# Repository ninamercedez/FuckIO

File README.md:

# FuckIO
An opensource fucking machine, that is far superiour to anything on the market.

## Specs
* Easy to built just with a 3D-printer, screwdrivers and easy-to-source parts.
* Completely 3D-printable with easy to print parts and almost no supports. Also avoiding tight tolerances to make this accessable as possible. 
* Simple, yet verastile mechanics.
* Based on a linear position drive, not a crank mechanism.
* Double 24V PWM output to drive external systems. Could be lube pumps, vibrators, etc.

## Mechanics
The mechanics is a direct derivative of an other open source project called OSSM. You can also find some informations about this build on their Discord.
https://github.com/KinkyMakers/OSSM-hardware

The motor mount is designed for a NEMA23 servo or stepper motor. Any motor fitting to this standart should work. 

### BOM
* iHSV57-30-18-36-... integrated servo motor from JMC
* 24V Power Brick Mean Well GST280A24-C6P 
* 40cm MGN12H linear rail
* 4x 605-2RS Z2 bearings
* Micro Switch
* GT2 20 Tooth Pulley for 8mm Axis and a 10mm belt
* GT2 belt with 10mm width
* Various M3 and M5 screws and nuts
* Arduino Nano33 IoT

## Electronics
The electronics board is used to interface an external stepper or servo controller. I can't drive a motor directly. It is based around an Arduino Nano33 IoT to enable BLE or WiFi support. It sends 5V DIR, PUL, ENA signals and expects FAULT signal and a homing switch. Two MOSFETs with freewheeling diodes allow PWM control of external systems running of the 24V supply.

## Firmware
The firmware uses a self developed stepper library. It uses the SAMD21 timer perihperials to generate the PUL signal. That way it is possible to create a much higher step rate with no processor loading. Popular Arduino libraries like AccelStepper are not up to the task.

__Do not use this firmware! It is heavly beeing worked on. It will destroy your hardware!__

## Control Software
No control software yet. But it is planned to use node-red in combination with MQTT messages.

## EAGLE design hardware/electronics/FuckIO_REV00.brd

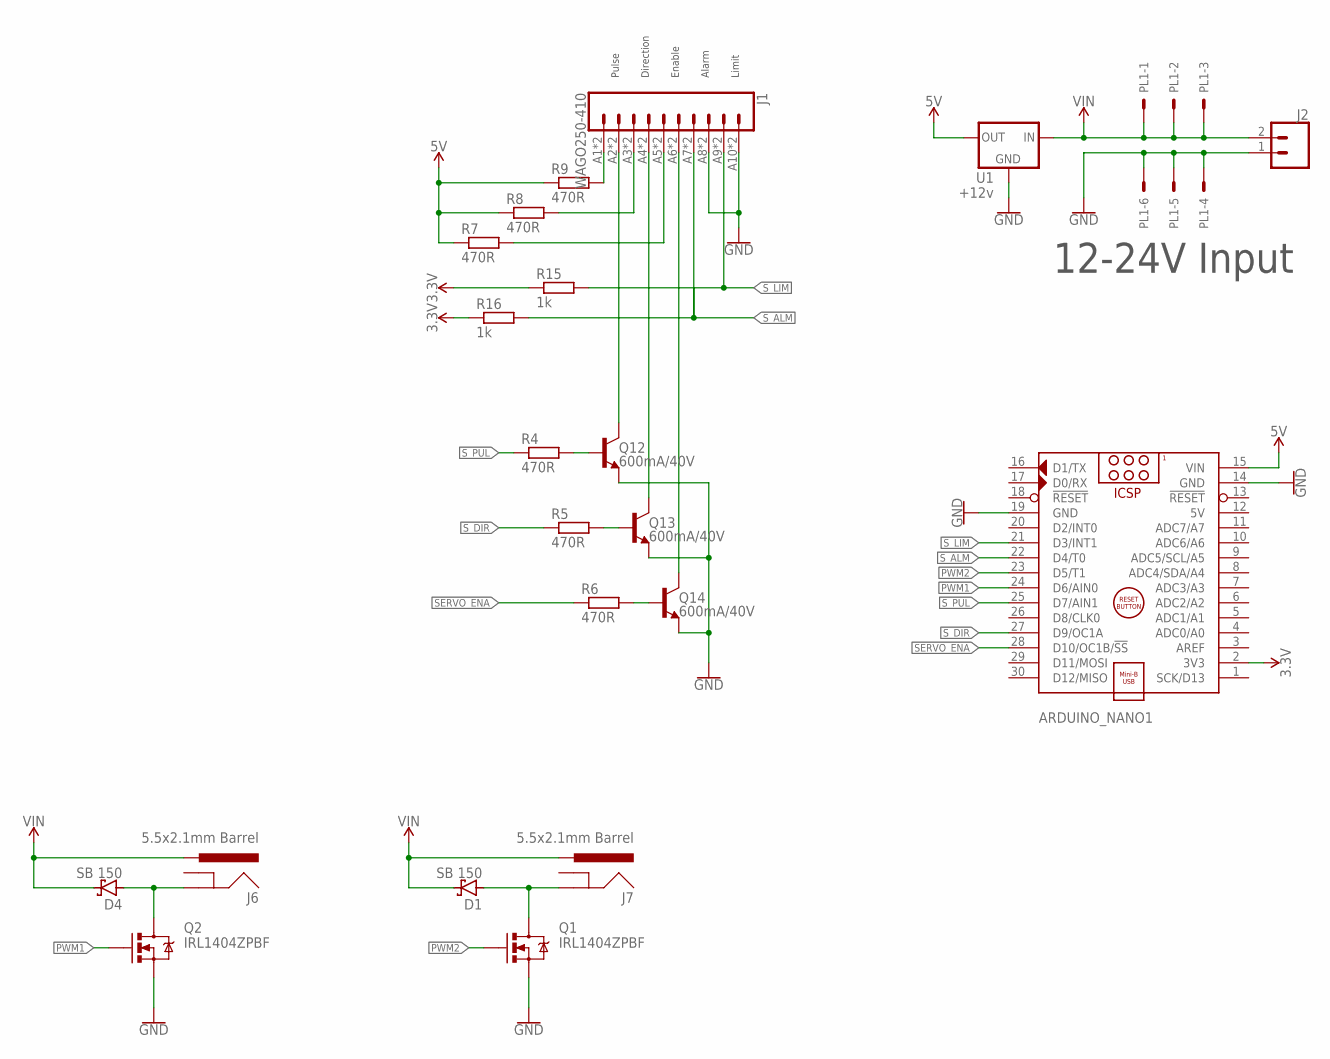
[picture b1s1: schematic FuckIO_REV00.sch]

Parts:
ARDUINO_NANO1: ARDUINO_NANO; ARDUINONANOV30_ARDUINO_NANO
D1, D4: SB 150; DIODE_DO41-10
J1: WAGO250-410; BEE_WAGO250-410
J2: CONN_025MM; SPARKFUN-CONNECTORS_SCREWTERMINAL-5MM-2
J6, J7: 5.5x2.1mm Barrel; SPARKFUN-CONNECTORS_POWER_JACK_PTH
PL1: CON-MOLEX-2_555X-6H; CON-MOLEX-2_5569-6
Q1, Q2: IRL1404ZPBF; BEE_TO220-IGO
Q12, Q13, Q14: 600mA/40V; SPARKFUN-DISCRETESEMI_TO-92
R4, R5, R6, R7, R8, R9: 470R; RCL_0204/5
R15, R16: 1k; RCL_0204/5
U1: +12v; SPARKFUN-IC-POWER_TO220-IGO

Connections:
3.3V: ARDUINO_NANO1.2 (3V3), R15.1, R16.1
5V: ARDUINO_NANO1.12 (5V), ARDUINO_NANO1.15 (VIN), R7.1, R8.1, R9.1, U1.OUT
GND: ARDUINO_NANO1.14 (GND), ARDUINO_NANO1.19 (GND), J1.A8 (8), J1.A10 (10), J1.B8 (8), J1.B10 (10), J2.1, PL1.4, PL1.5, PL1.6, Q1.S, Q2.S, Q12.3 (E), Q13.3 (E), Q14.3 (E), U1.GND
unnamed: J1.A5 (5), J1.B5 (5), R7.2
unnamed: J1.A3 (3), J1.B3 (3), R8.2
unnamed: J1.A1 (1), J1.B1 (1), R9.2
unnamed: J1.A6 (6), J1.B6 (6), Q14.1 (C)
unnamed: J1.A4 (4), J1.B4 (4), Q13.1 (C)
unnamed: J1.A2 (2), J1.B2 (2), Q12.1 (C)
unnamed: Q12.2 (B), R4.2
unnamed: Q13.2 (B), R5.2
unnamed: Q14.2 (B), R6.2
unnamed: D4.A, J6.GND, Q2.D
unnamed: D1.A, J7.GND, Q1.D
PWM1: ARDUINO_NANO1.24 (D6/AIN0), Q2.G
PWM2: ARDUINO_NANO1.23 (D5/T1), Q1.G
SERVO_ENA: ARDUINO_NANO1.28 (D10/OC1B/!SS), R6.1
S_ALM: ARDUINO_NANO1.22 (D4/T0), J1.A7 (7), J1.B7 (7), R16.2
S_DIR: ARDUINO_NANO1.27 (D9/OC1A), R5.1
S_LIM: ARDUINO_NANO1.21 (D3/INT1), J1.A9 (9), J1.B9 (9), R15.2
S_PUL: ARDUINO_NANO1.25 (D7/AIN1), R4.1
VIN: D1.C, D4.C, J2.2, J6.PWR, J7.PWR, PL1.1, PL1.2, PL1.3, U1.IN

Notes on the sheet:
Pulse
Direction
Enable
Alarm
12-24V Input
Limit

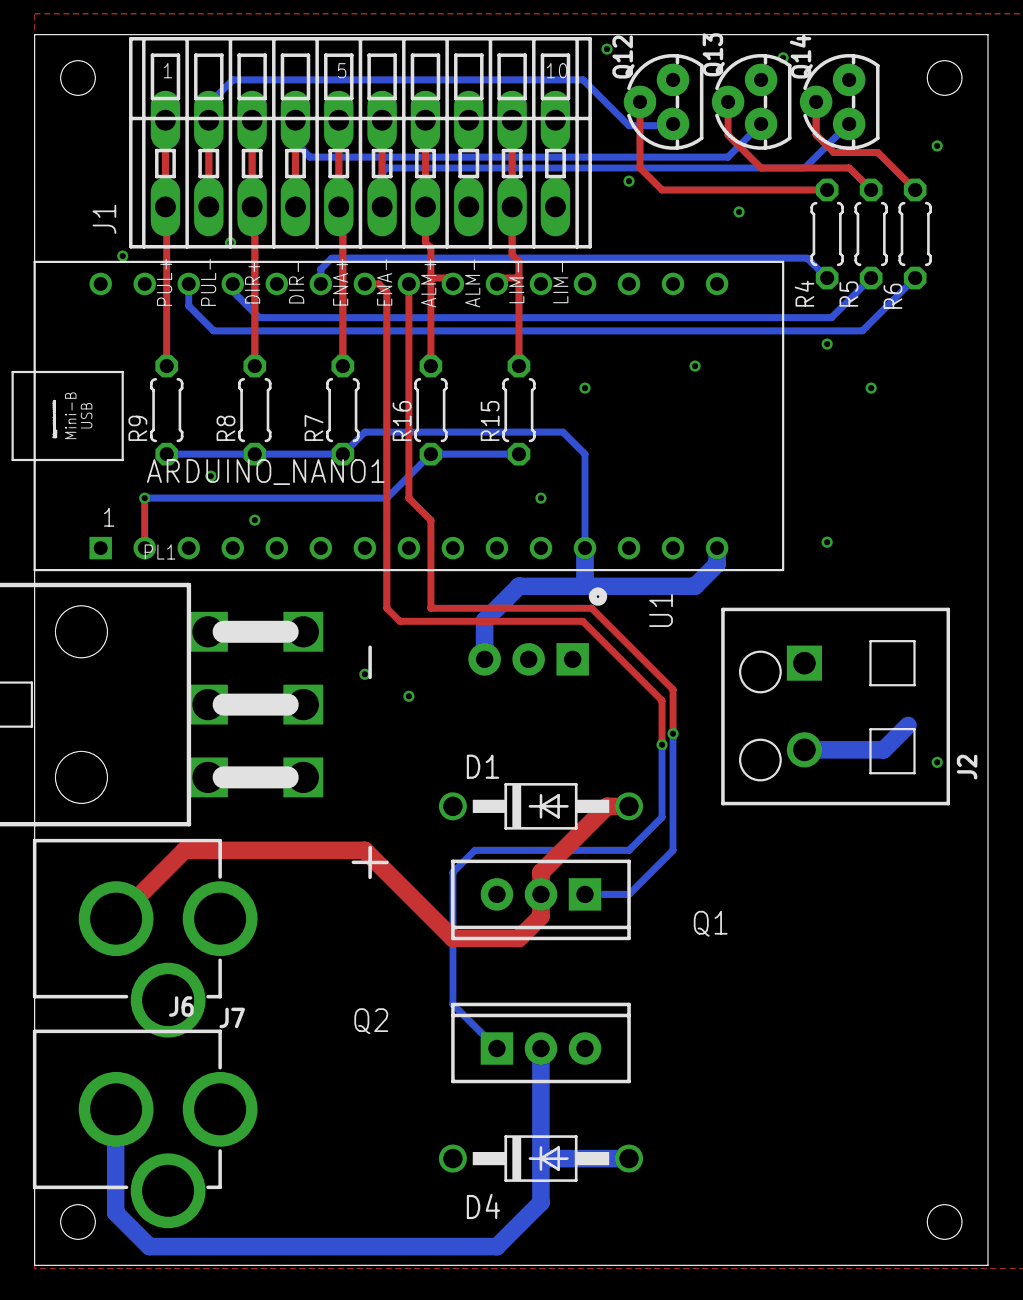
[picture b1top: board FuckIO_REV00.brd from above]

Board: 2 copper layers, 55.0 x 71.0 mm, 22 parts (0 on the bottom side), 22 nets.

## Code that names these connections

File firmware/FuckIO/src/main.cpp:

#include <Arduino.h>
#include <SPI.h>
#include <WiFiNINA.h>
#include <MQTT.h>
#include <SAMD21Step.h> 
#include <MotionCtrl.h>



// Pin Definitions
const int S_PUL = 11;
const int SE_PUL = 7;
const int S_DIR = 9;
const int SE_DIR = A2;
const int SERVO_ENA = 10;
const int S_LIM = 3;
const int SE_LIM = A7;
const int S_ALM = 4;
const int SE_ALM = A1;

const int PWM1 = 6;
const int PWM2 = 5;

// Servo Settings:
#define STEP_PER_REV      3200   // How many steps per revolution of the motor (S1 on)
#define PULLEY_TEETH      15     // How many teeth has the pulley
#define BELT_PITCH        3      // What is the timing belt pitch in mm
#define MAX_TRAVEL        200    // What is the maximum physical travel in mm
#define KEEPOUT_BOUNDARY  5      // Soft endstop preventing hard crashes in mm. Will be 
                                 // subtracted twice from MAX_TRAVEL
#define MAX_RPM           2900   // What is the maximum RPM of the servo
#define MAX_ACC           30000  // Maximum acceleration in mm/s^2
#define INVERSE           false  // Set to true to invert the direction signal
                                 // The firmware expects the home switch to be located at the 
                                 // end of an retraction move. That way the machine homes 
                                 // itself away from the body.

// Derived Servo Settings
#define STEP_PER_MM       STEP_PER_REV / (PULLEY_TEETH * BELT_PITCH)
#define TRAVEL            MAX_TRAVEL - (2 * KEEPOUT_BOUNDARY)
#define MIN_STEP          int(0.5 + KEEPOUT_BOUNDARY * STEP_PER_MM)
#define MAX_STEP          int(0.5 + (MAX_TRAVEL - KEEPOUT_BOUNDARY) * STEP_PER_MM)
#define MAX_STEP_PER_SEC  int(0.5 + (MAX_RPM * STEP_PER_REV) / 60)
#define MAX_STEP_ACC      int(0.5 + MAX_ACC * STEP_PER_MM)

// Coniguration of the stepper motor
StepperConfig stepper0config = {
  .pulsePin = S_PUL,                   // Arduino pin number for the pulse pin. Must be a pin with a TCC timer output (see PinLookup). One timer can exclusivly serve only one pin.
  .dirPin = S_DIR,                     // Arduino pin number of the direction signal. May be any pin.
  .enablePin = SERVO_ENA,              // Arduino pin number of the driver enable signal. May be any pin. Set to -1 if not used.
  .enableActiveLow = true,             // Set to true if the enable signal is active low. For active high set to false.
  .alarmPin = S_ALM,                   // Arduino pin number of the driver alarm signal. Must be an interrupt pin. Set to -1 if not used.
  .alarmActiveHigh = true,             // Set to true if the alarm signal is active high. For active low set to false.
  .homePin = S_LIM,                    // Arduino pin number of the home switch. Must be an interrupt pin. Homing is mandatory
  .homeActiveHigh = true,              // Set to true if the home signal is active high. For active low set to false.
  .invertPulse = true,                 // Set to true if you need an active low pulse signal
  .minPulseWidth = 4.0,                // Minimum pulse width in µs
  .maxVelocity = MAX_STEP_PER_SEC,     // Maximum velocity in steps/sec
  .maxAcceleration = MAX_STEP_ACC,     // Maximum accelceration & decceleratin in steps/sec^2
  .minPosition = MIN_STEP,             // Minimum position of the axis in steps
  .maxPosition = MAX_STEP,             // Maximum position of the axis in steps
  .homePosition = 0,                   // The position of home. When the home switch is triggered position will be set to this value. May be outside the minPosition and maxPosition boundary
  .invertDirection = false,            // Set to true to invert the movement direction
  .invertHoming = false                // Set to true to invert the direction for searching the home switch
};

// timer tester
Stepper stepper0;
MotionCtrl& motion = MotionCtrl::instance();

void setup() {
  pinMode(LED_BUILTIN, OUTPUT);

  Serial.begin(115200);
  while (!Serial) {
    delay(10);
  }
  
  Serial.println("Timer callback tester");

  stepper0.begin(&stepper0config);
  motion.begin(5.0, &stepper0);
  
  stepper0.enableDriver(true);
}

void loop() {

}





/*
WiFiClient net;
MQTTClient client(128); //The passed value denotes the read and write buffer size.

char ssid[] = "Kellerkind";
char pass[] = "Putzplan"; 
byte mac[6]; // the MAC address of your Wifi shield

char host[] = "192.168.1.24"; // Note: Local domain names (e.g. "Computer.local" on OSX) are not supported by Arduino. You need to set the IP address directly.
char user[] = "";
char pwd[] = "";
char clientID[] = "FuckIO"; //MQTT ClientID
char topic[] = "FuckIO/control/+";

unsigned int currentMillis = 0;
unsigned int startMillis = 0;
unsigned int microsPulses = 125;

void messageReceived(String &topic, String &payload) { 
bool bvalue = false;
  Serial.println("Message: " + topic + " - " + payload);
  if (topic.startsWith("FuckIO/control")) {
    topic.remove(0, topic.lastIndexOf('/') + 1);
    if (topic.equals("run")) {
      bvalue = payload.equalsIgnoreCase("TRUE");
      digitalWrite(SERVO_ENA, bvalue);  // Enable or disable the servo motors
      digitalWrite(LED_BUILTIN, bvalue);  // Enable or disable the servo motors
      // Handle Timer
    }
    if (topic.equals("rpm")) {
      microsPulses = int((1.0/((payload.toInt() / 60.0)*8000))*1000000);
      Serial.println(microsPulses);
    }
    if (topic.equals("dir")) {
      bvalue = payload.equalsIgnoreCase("TRUE");
      digitalWrite(S_DIR, bvalue);  // CW / CWW rotation
      digitalWrite(SE_DIR, bvalue);  // CW / CWW rotation
    }
    if (topic.equals("pwm")) {
      analogWrite(PWM1, constrain(payload.toInt(), 0, 255));
      analogWrite(PWM2, constrain(payload.toInt(), 0, 255));
    }
  }
}

void connect() {
  String macAdress = "";

  WiFi.begin(ssid, pass);

  Serial.print("connecting WiFi ");
  while (WiFi.status() != WL_CONNECTED) {
    Serial.print(".");
    delay(500);
  }

  // print the SSID of the network you're attached to:
  Serial.print("\nSSID: ");
  Serial.println(WiFi.SSID());

  // print your WiFi shield's IP address:
  IPAddress ip = WiFi.localIP();
  Serial.print("IP Address: ");
  Serial.println(ip);

  // print your MAC address:
  WiFi.macAddress(mac);
  Serial.print("MAC Address: ");
  Serial.print(mac[5],HEX);
  Serial.print(":");
  Serial.print(mac[4],HEX);
  Serial.print(":");
  Serial.print(mac[3],HEX);
  Serial.print(":");
  Serial.print(mac[2],HEX);
  Serial.print(":");
  Serial.print(mac[1],HEX);
  Serial.print(":");
  Serial.println(mac[0],HEX);

  // print the received signal strength:
  long rssi = WiFi.RSSI();
  Serial.print("signal strength (RSSI): ");
  Serial.print(rssi);
  Serial.println(" dBm");

  client.begin(host, net);

  Serial.print("connecting to MQTT-Server " + String(host));
  while (client.connect(clientID, user, pwd) == false) {
    Serial.print("*");
    delay(500);
  }

  Serial.println("\nsubscribing to " + String(topic));
  client.onMessage(messageReceived);
  if (client.subscribe(topic))
  {
    Serial.println("Success");
  } else
  {
    Serial.println("\nCouldn't subscribe");
  } 

  client.publish("/hello", "world");

}

void setup() {

  // Initialize Pins
  pinMode(S_PUL, OUTPUT);
  pinMode(SE_PUL, OUTPUT);
  pinMode(S_DIR, OUTPUT);
  pinMode(SE_DIR, OUTPUT);
  digitalWrite(S_DIR, HIGH);
  digitalWrite(SE_DIR, HIGH);
  pinMode(SERVO_ENA, OUTPUT);
  digitalWrite(SERVO_ENA, LOW);  //Disarm the servo motors
  pinMode(S_LIM, INPUT);
  pinMode(SE_LIM, INPUT);
  pinMode(S_ALM, INPUT);
  pinMode(SE_ALM, INPUT);
  pinMode(PWM1, OUTPUT);
  pinMode(PWM2, OUTPUT);
  pinMode(LED_BUILTIN, OUTPUT);
  digitalWrite(LED_BUILTIN, HIGH);

  Serial.begin(115200);
  connect();
}

void loop() {
    
  currentMillis = millis();
  
  if (currentMillis - startMillis >= 100) {
    startMillis = currentMillis;
    client.loop();
    Serial.println("signal strength (RSSI): " + WiFi.RSSI());

    if (!client.connected()) {
      Serial.println("Lost connection! Try to reconnect.");
      connect();
    }
  }

  digitalWrite(S_PUL, HIGH);
  digitalWrite(SE_PUL, HIGH);
  delayMicroseconds(microsPulses);
  digitalWrite(S_PUL, LOW);
  digitalWrite(SE_PUL, LOW);
  delayMicroseconds(microsPulses);

}
*/

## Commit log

2020-06-21 Create LICENCE
2021-03-07 New hardware design
    Changed hardware inspired by OSSM project
